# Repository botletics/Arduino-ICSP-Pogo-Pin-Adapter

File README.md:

<h1>Arduino ICSP Pogo Pin Adapter</h1>

## Overview

The ISP (or ICSP) pogo pin adapter is geared toward hobbyists who love to design their own PCB's and program them with an Arduino!
It is specifically designed for Atmel microcontrollers that are programmable via SPI and is very useful for
flashing the Arduino bootloader to the chip. The only thing you have to do is design your PCB with six test
point pads placed in a standard 2x3 ICSP configuration with 2.54mm (0.1") spacing.

You can order a loose kit or fully-assembled adapter [here](https://www.botletics.com/products/icsp-pogo-adapter)

Also check out the full wiki [here](https://github.com/botletics/Arduino-ICSP-Pogo-Pin-Adapter/wiki)

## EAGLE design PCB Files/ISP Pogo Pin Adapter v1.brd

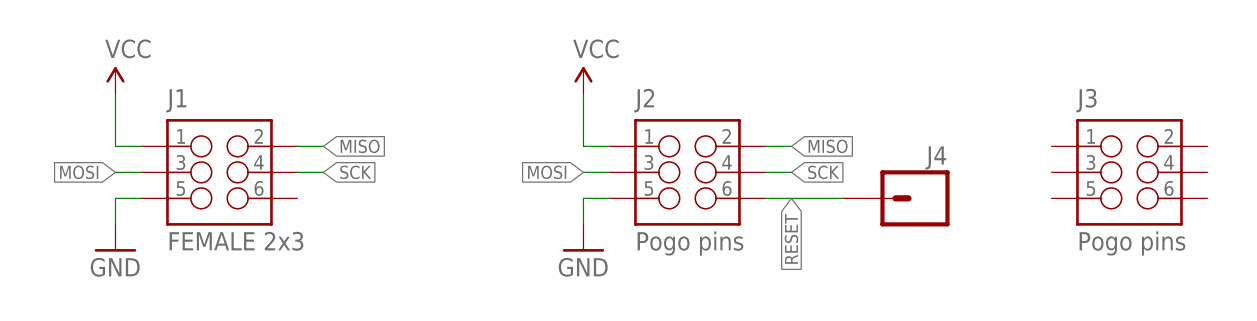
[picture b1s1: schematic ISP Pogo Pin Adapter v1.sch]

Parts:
J1: FEMALE 2x3; 2X3
J2, J3: Pogo pins; 2X3_POGO
J4: M01PTH; 1X01

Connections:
GND: J1.5, J2.P$5 (5)
MISO: J1.2, J2.P$2 (2)
MOSI: J1.3, J2.P$3 (3)
RESET: J2.P$6 (6), J4.1
SCK: J1.4, J2.P$4 (4)
VCC: J1.1, J2.P$1 (1)

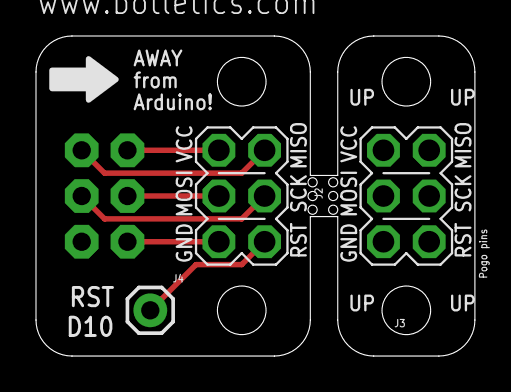
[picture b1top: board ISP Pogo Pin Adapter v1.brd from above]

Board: 2 copper layers, 24.4 x 17.8 mm, 4 parts (1 on the bottom side), 6 nets.

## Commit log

2017-09-23 Create Images
2017-09-23 Create Image
2017-09-23 Create blah
